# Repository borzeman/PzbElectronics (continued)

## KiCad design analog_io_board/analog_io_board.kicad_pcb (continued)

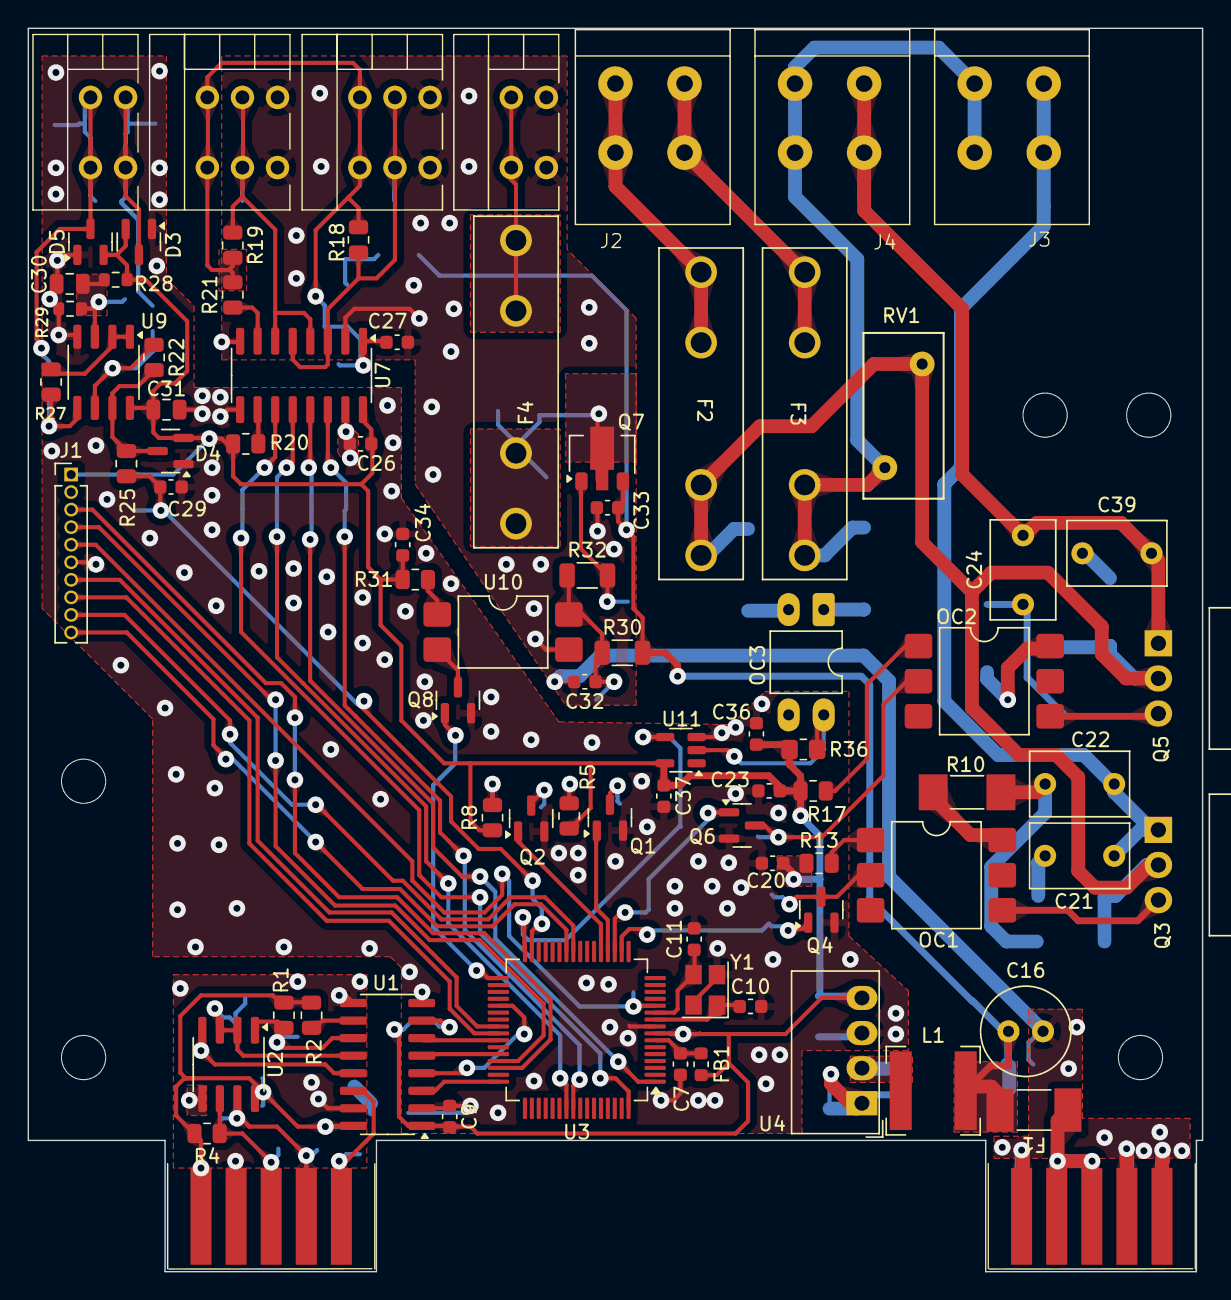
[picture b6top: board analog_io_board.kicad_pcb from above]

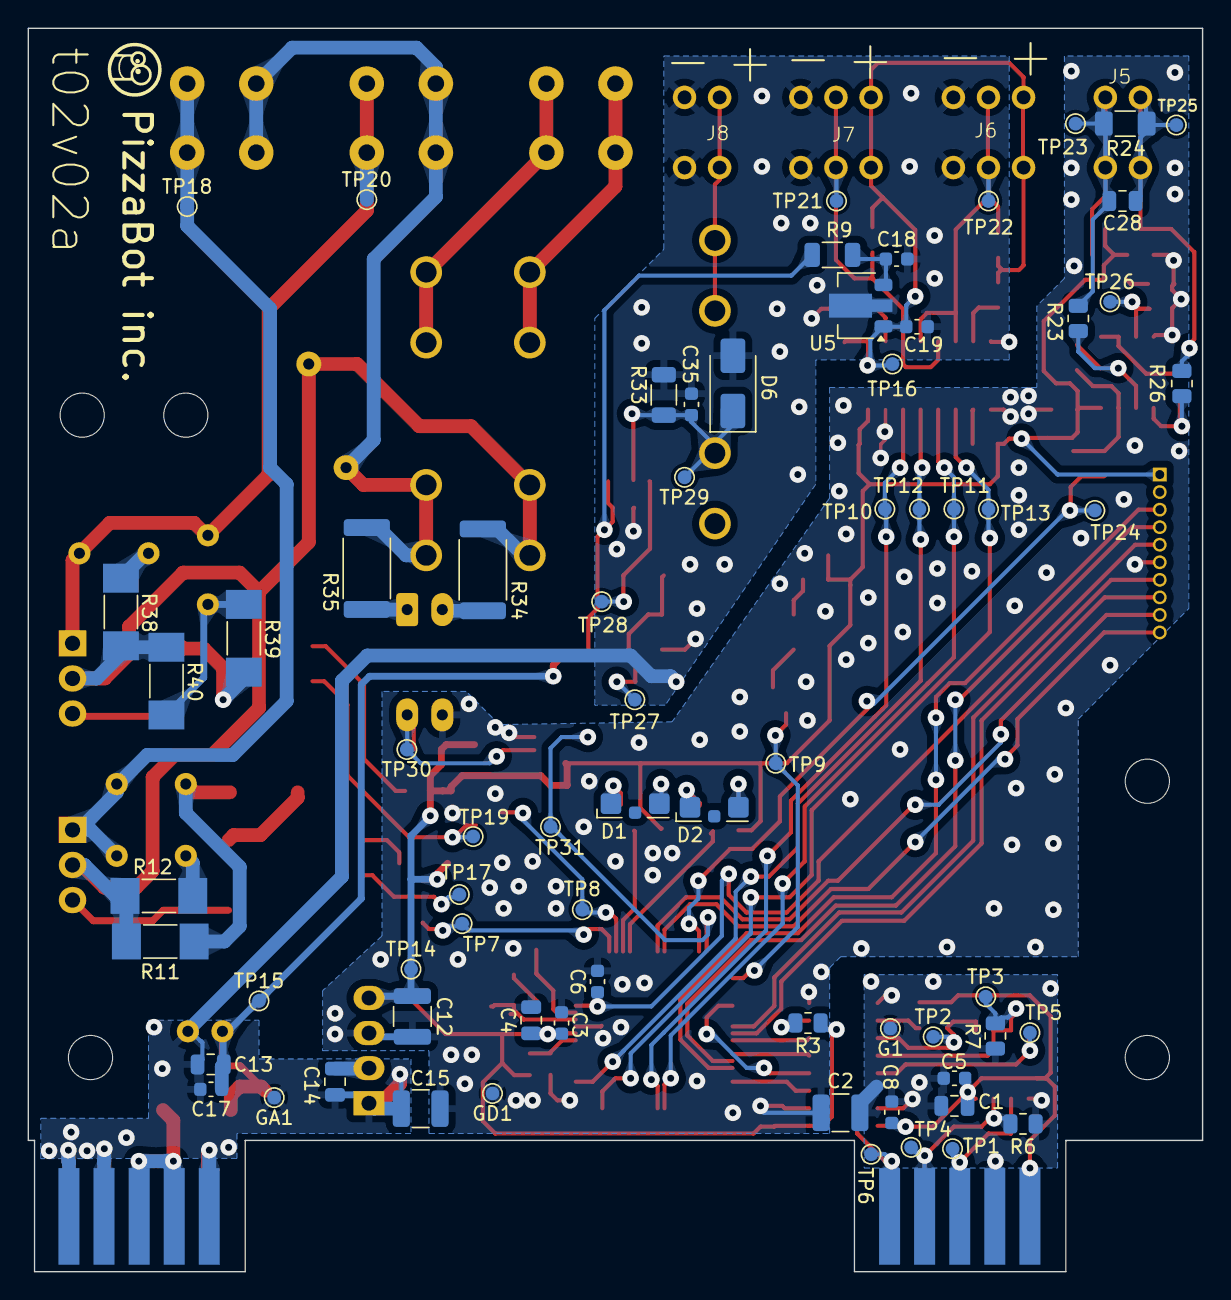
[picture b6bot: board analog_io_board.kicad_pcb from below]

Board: 2 copper layers, 85.0 x 90.0 mm, 156 parts (69 on the bottom side), 85 nets.

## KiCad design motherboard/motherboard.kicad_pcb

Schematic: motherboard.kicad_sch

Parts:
D1, D2, D3, D4, D5, D6, D7, D8, D9, D10: SMBJ5.0A (SMB); D_SMB
H1, H2, H3, H4, H5, H6, H7, H8, H9, H10, H11, H12, H13, H14: MountingHole_M3_3.2mm_Pad; MountingHole_3.2mm_M3
J1, J2, J4, J5, J6, J7, J8, J9, J10, J11, J12, J13, J14, J15, J16, J17, J18, J19, J20, J21, J22, J23, J24, J25: SL-10 (L-KLS1-603C-10-S)
J3: SL-14 (L-KLS1-603C-14-S)
J28: PinHeader_1x02_P2.54mm (Contr +24V); PinHeader_1x02_P2.54mm_Vertical
J29: PinHeader_1x04_P2.54mm (RS485); PinHeader_1x04_P2.54mm_Vertical
J30: PinHeader_2x07_P2.54mm (RTS); PinHeader_2x07_P2.54mm_Vertical
L2: B82790S0253N201; L_CommonMode_Delevan_4222
R1: 1206-120 Ом±5%-0,25 Вт; R_1206_3216Metric
RV1, RV2, RV3, RV4, RV5: JMV0805S5R6T661; R_0805_2012Metric
TP1, TP2, TP3, TP17: TestPoint; TestPoint_Pad_D1.0mm
TP4, TP5, TP6, TP7, TP8, TP9, TP10, TP11, TP12, TP13, TP14, TP15, TP16: TestPoint; TestPoint_D1

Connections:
+24V: J2.2, J2.3, J2.8, J2.9, J5.2, J5.3, J5.8, J5.9, J7.2, J7.3, J7.8, J7.9, J9.2, J9.3, J9.8, J9.9, J11.2, J11.3, J11.8, J11.9, J13.2, J13.3, J13.8, J13.9, J15.2, J15.3, J15.8, J15.9, J17.2, J17.3, J17.8, J17.9, J19.2, J19.3, J19.8, J19.9, J21.2, J21.3, J21.8, J21.9, J23.2, J23.3, J23.8, J23.9, J25.2, J25.3, J25.8, J25.9, J28.2, TP16.1; also elsewhere on the board
/+3.3VRS485: J1.1, J1.10, J4.1, J4.10, J6.1, J6.10, J8.1, J8.10, J10.1, J10.10, J12.1, J12.10, J14.1, J14.10, J16.1, J16.10, J18.1, J18.10, J20.1, J20.10, J22.1, J22.10, J24.1, J24.10, J29.1, TP15.1; also elsewhere on the board
/A: D1.1 (K), D4.1 (K), D6.1 (K), D8.1 (K), D10.1 (K), J4.3, J4.8, J6.3, J6.8, J8.3, J8.8, J10.3, J10.8, J12.3, J12.8, J14.3, J14.8, J16.3, J16.8, J18.3, J18.8, J20.3, J20.8, J22.3, J22.8, J24.3, J24.8, J29.3, L2.3, R1.1, RV1.1, RV2.1, RV3.1, RV4.1, RV5.1, TP1.1
/B: D2.1 (K), D3.1 (K), D5.1 (K), D7.1 (K), D9.1 (K), J4.4, J4.7, J6.4, J6.7, J8.4, J8.7, J10.4, J10.7, J12.4, J12.7, J14.4, J14.7, J16.4, J16.7, J18.4, J18.7, J20.4, J20.7, J22.4, J22.7, J24.4, J24.7, J29.4, L2.4, R1.2, RV1.2, RV2.2, RV3.2, RV4.2, RV5.2, TP2.1
/RTS1: J3.1, J4.5, J4.6, J30.1, TP3.1
/RTS2: J3.14, J6.5, J6.6, J30.2, TP9.1
/RTS3: J3.2, J8.5, J8.6, J30.3, TP4.1
/RTS4: J3.13, J10.5, J10.6, J30.4, TP10.1
/RTS5: J3.3, J12.5, J12.6, J30.5, TP5.1
/RTS6: J3.12, J14.5, J14.6, J30.6, TP11.1
/RTS7: J3.4, J16.5, J16.6, J30.7, TP6.1
/RTS8: J3.11, J18.5, J18.6, J30.8, TP12.1
/RTS9: J3.5, J20.5, J20.6, J30.9, TP7.1
/RTS10: J3.10, J22.5, J22.6, J30.10, TP13.1
/RTS11: J3.6, J24.5, J24.6, J30.11, TP8.1
/RTS12: J3.9, J30.12
GND1: D1.2 (A), D2.2 (A), D3.2 (A), D4.2 (A), D5.2 (A), D6.2 (A), D7.2 (A), D8.2 (A), D9.2 (A), D10.2 (A), J1.2, J1.5, J1.6, J1.9, J3.7, J3.8, J4.2, J4.9, J6.2, J6.9, J8.2, J8.9, J10.2, J10.9, J12.2, J12.9, J14.2, J14.9, J16.2, J16.9, J18.2, J18.9, J20.2, J20.9, J22.2, J22.9, J24.2, J24.9, J29.2, J30.13, J30.14, TP17.1; also elsewhere on the board
GNDA: J2.1, J2.4, J2.5, J2.6, J2.7, J2.10, J5.1, J5.4, J5.5, J5.6, J5.7, J5.10, J7.1, J7.4, J7.5, J7.6, J7.7, J7.10, J9.1, J9.4, J9.5, J9.6, J9.7, J9.10, J11.1, J11.4, J11.5, J11.6, J11.7, J11.10, J13.1, J13.4, J13.5, J13.6, J13.7, J13.10, J15.1, J15.4, J15.5, J15.6, J15.7, J15.10, J17.1, J17.4, J17.5, J17.6, J17.7, J17.10, J19.1, J19.4, J19.5, J19.6, J19.7, J19.10, J21.1, J21.4, J21.5, J21.6, J21.7, J21.10, J23.1, J23.4, J23.5, J23.6, J23.7, J23.10, J25.1, J25.4, J25.5, J25.6, J25.7, J25.10, J28.1, TP14.1; also elsewhere on the board
unnamed: J1.3, J1.8, L2.2
unnamed: J1.4, J1.7, L2.1

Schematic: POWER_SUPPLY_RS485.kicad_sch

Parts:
C3: 10uF 50V 1210 GRM32ER71H106K; C_1210_3225Metric
C4, C5: 4,7uF 50V 0805; C_0805_2012Metric
C6: 270 pf X7R 1206 2000v 202R18W271KW4E; C_1210_3225Metric
D14: LED 0805 (FYLS-0805UBC); LED_0805_2012Metric_Pad1.15x1.40mm_HandSolder
L1: 6,8uH 3,5A ETQP3M6R8KVP; L_Bourns-SRN6028
R8: 0805-200 Ом±5%-0,125 Вт; R_0805_2012Metric
U2: AM1SS-2403SJZ; Converter_DCDC_Murata_CRE1xxxxxx3C_THT

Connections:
+24V: C4.1, L1.1; also elsewhere on the board
/+3.3VRS485: C3.1, D14.2 (A), U2.4 (OUT+); also elsewhere on the board
GND1: C3.2, C6.2, R8.2, U2.3 (OUT-); also elsewhere on the board
GNDA: C4.2, C5.2, C6.1, U2.1 (IN-); also elsewhere on the board
unnamed: D14.1 (K), R8.1
unnamed: C5.1, L1.2, U2.2 (IN+)

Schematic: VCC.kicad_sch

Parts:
C1, C2: 47uF 63V D10 H16; CP_Radial_D10.0mm_P5.00mm
C7: 0,01uF 50V 0805; C_0805_2012Metric
D11: SM6T27CA (SMB); D_SMB
D12: LED 0805 (FYLS-0805UBC); LED_0805_2012Metric_Pad1.15x1.40mm_HandSolder
D13: BZX84C10 (SOT-23); SOT-23
F1, F2: Fuse 5A ZH266 (2 клипсы); Fuseholder_Littelfuse_100_series_5x20mm
FL1: ACM70V-701-2PL-TL00; ACM12V
J26, J27: DG142V-5.08-02P-14
Q1, Q3: SUM110P06-08L-E3 (TO-263-2); TO-263-2
Q6: PMBT3906; SOT-23-3
Q7: TS820-600B; TO-252-2
R2: 2512-2,4 кОм±5%-1 Вт; R_2512_6332Metric
R3, R7, R12: 0805-10 кОм±5%-0,125 Вт; R_0805_2012Metric
R4: 0805-1,5 кОм±5%-0,125 Вт; R_0805_2012Metric
R5, R6: 1206-1 кОм±5%-0,25 Вт; R_1206_3216Metric
R9: 0805-100 кОм±5%-0,125 Вт; R_0805_2012Metric
R10: 0805-11 кОм±5%-0,125 Вт; R_0805_2012Metric
R11: 1206-3,3 кОм±5%-0,25 Вт; R_1206_3216Metric
R13: 0805-7,5 кОм±5%-0,125 Вт; R_0805_2012Metric
R14: 0805-1 кОм±5%-0,125 Вт; R_0805_2012Metric
R15: 0805-56 кОм±5%-0,125 Вт; R_0805_2012Metric
TP18, TP19: TestPoint; TestPoint_Pad_D1.0mm
TP20: TestPoint; TestPoint_D1
U1, U3: TL431DBZ (sot-23); SOT-23

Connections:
+24V: C2.1, D12.2 (A), FL1.4; also elsewhere on the board
GNDA: C2.2, FL1.3, R2.2; also elsewhere on the board
unnamed: D11.1 (A1), F1.1, Q3.2 (D), Q7.2 (A), R9.1, R11.1, R13.1
unnamed: C1.2, C7.2, D11.2 (A2), F2.1, FL1.2, Q7.1 (K), R4.2, R7.2, R10.2, R14.2, R15.2, TP20.1, U1.3 (A), U3.3 (A)
unnamed: D12.1 (K), R2.1
unnamed: D13.1 (A), Q3.1 (G), R7.1
unnamed: D13.3 (K), Q1.3 (S), Q3.3 (S), R3.1, R5.1, TP19.1
unnamed: F1.2, J26.1, J26.2
unnamed: F2.2, J27.1, J27.2
unnamed: C1.1, FL1.1, Q1.2 (D), TP18.1
unnamed: Q1.1 (G), R5.2, R6.1
unnamed: Q6.1 (B), R12.2
unnamed: C7.1, Q6.3 (C), Q7.3 (G), R14.1
unnamed: Q6.2 (E), R13.2
unnamed: R6.2, U1.1 (K)
unnamed: R3.2, R4.1, U1.2 (REF)
unnamed: R11.2, R12.1, U3.1 (K)
unnamed: R9.2, R10.1, R15.1, U3.2 (REF)

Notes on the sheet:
защита от обратной полярности
10V
защита от низкого напряжения
напряжение в открытом состоянии 0,9V
защита от перенапряжения
2,5V срабатывания
1.2mA
0,125mA 15V

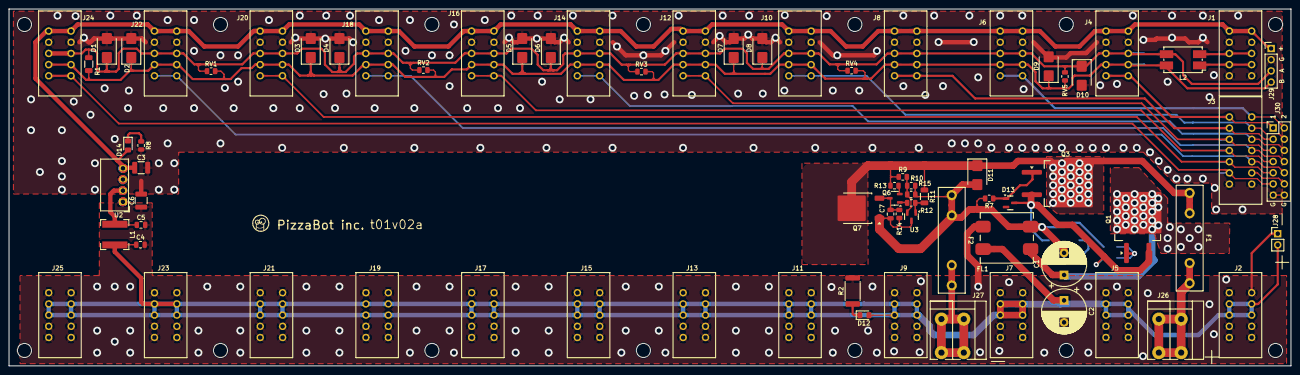
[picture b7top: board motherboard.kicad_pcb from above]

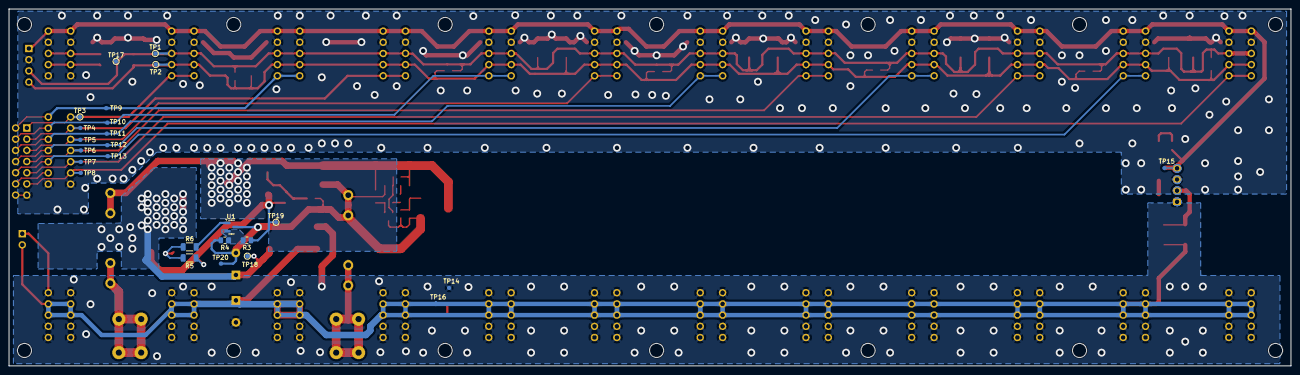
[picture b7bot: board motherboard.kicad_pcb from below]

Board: 2 copper layers, 291.0 x 81.0 mm, 117 parts (25 on the bottom side), 38 nets.

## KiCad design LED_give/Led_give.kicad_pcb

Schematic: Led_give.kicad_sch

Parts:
C1: 100uF 50V 10x10,5(JCK1H101M100105); CP_Elec_10x10.5
C2, C3, C4: 0,1uF 100V 0805; C_0805_2012Metric
D1, D2, D3: BZV55B10; D_MiniMELF
F1: Fuse 5A ZH266 (2 клипсы); Fuseholder_100_series_5x20mm_D1,5
H1, H2: MountingHole; MountingHole_3.2mm_M3_Pad
J1: DG141R-2.54-02P-14-00; DG141R-04
J2: DG142R-5.08-04P-14
J3: DG142R-5.08-02P-14
Q1, Q2, Q3: 50N06; TO-252-2
R1, R3, R5: 203; R_0805_2012Metric
R2, R4, R6: 752; R_0805_2012Metric

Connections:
+24V: C1.1, F1.1, J2.1
/Bin: C4.1, J1.4, R5.1
/Bout: J2.4, Q3.2 (D)
/Gin: C3.1, J1.3, R3.1
/Gout: J2.3, Q2.2 (D)
/Rin: C2.1, J1.2, R1.1
/Rout: J2.2, Q1.2 (D)
GND: C1.2, C2.2, C3.2, C4.2, D1.2 (A), D2.2 (A), D3.2 (A), J1.1, J3.2, Q1.3 (S), Q2.3 (S), Q3.3 (S), R2.1, R4.1, R6.1
unnamed: D1.1 (K), Q1.1 (G), R1.2, R2.2
unnamed: D2.1 (K), Q2.1 (G), R3.2, R4.2
unnamed: D3.1 (K), Q3.1 (G), R5.2, R6.2
unnamed: F1.2, J3.1

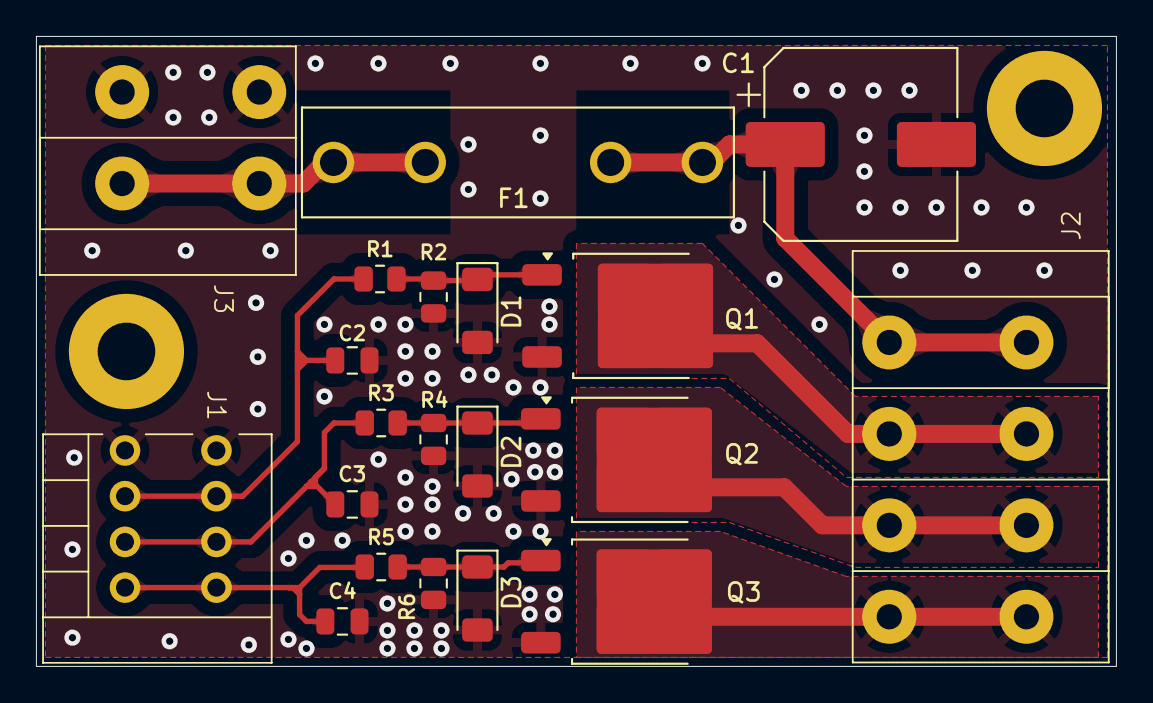
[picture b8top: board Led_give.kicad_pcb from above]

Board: 2 copper layers, 60.0 x 35.0 mm, 22 parts (0 on the bottom side), 12 nets.

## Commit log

2024-04-30 Added technical specifications
2024-04-30 Загрузка файлов первоначальная
2024-04-30 add txt
2024-04-30 add first file
2024-05-01 MB added protect,LED
2024-05-01 deleted unnecessary file
2024-05-04 Modify Digit_IN, Motherbord, Step motors
2024-05-07 Modify Digit_IN, Motherbord, Step motors, photo
2024-05-20 Modify Motherbord Schems and PCB
2024-05-20 Modify Motherbord Schems and PCB1
2024-05-22 Modify MainController Schems and PCB1
2024-05-22 Modify Pump Schems and PCB1
2024-05-22 Modify Triac Schems and PCB1
2024-05-22 Modify StepMotor Schems and PCB1
2024-05-22 Modify DiscretIN Schems and PCB1
2024-05-27 Modify Mian controller, stepmotor, motor 25.05.24
2024-06-03 Add DE USART 03.06.24
2024-06-03 Change ISOLATOR 03.06.24
2024-06-05 pcb and schems step 05.06.24
2024-06-07 pcb and schems main controller 07.06.24
2024-06-10 renew motherbord (tvs) and new dc_motors 10.06.24
2024-06-10 stepmotor add r41 10.06.24
2024-06-11 Discret IN OUT schems
2024-06-13 LED PhotoTrans schems and PCB
2024-06-17 Triak schems and PCB
2024-06-18 Change TVS diods near optopair schems and PCB
2024-06-18 add analog board reqs
2024-06-18 Main controller +3.3V RS485 schems and PCB
2024-06-25 DIgit_IN renew schems
2024-06-26 Main controller renew schems and PCB
2024-06-26 renew schems
2024-06-27 remove excess files
2024-06-27 fotodiod sborochniy1
2024-06-27 DC motor schems
2024-06-28 Discret IN_OUT schems and PCB
2024-07-02 Renew footprint connectors PCB
2024-07-03 Renew pin Prog connectors and schem Analog IO
2024-07-04 digit IO terned LED
2024-07-05 renew all schems and pcb for production
2024-07-10 add relay control to analog board requirements
2024-07-10 PCB AND SCHEMS DC MOTOR
2024-07-11 analog io control relay added
2024-07-11 analog io control relay added1
2024-07-17 anlog IO pcb and shcems
2024-07-18 add reqs to analog board to make it suitable for fridge control
2024-07-19 anlog IO shcems 2.0
2024-07-22 anlog IO shcems 2.1
2024-07-23 QR code schems
2024-07-23 RENEW Analog IO schems
2024-07-25 QR board reqs
2024-07-26 qr code 1.1
2024-07-27 analog board add mech relay diode requirement
2024-07-27 Remove relay signal current limiting requirement
2024-07-28 RENEW ALL BOARDS
2024-07-31 CHANGE CONNECTORS ON DG245
2024-08-01 IO ANALOG PCB
2024-08-08 qr code schems and pcb
2024-08-12 update qr reqs
2024-08-23 qr and analog refresh
2024-09-26 fix "pia" typo
2024-10-03 rename files to snake case matching with their dir
2024-11-18 DCmotors V1.5
2024-11-20 add manipulator attachment scheme
2024-11-20 fix dc board issues before manufacturing
2024-11-21 DC, contr, mb, step v2
2024-11-21 digit_in v2
2024-11-25 DC, contr, mb, digit in v2.1
2024-11-26 step v2.1
2024-11-27 Triak v2.1
2024-11-29 manipulator 1.0
2024-12-02 controller убраны ловушки
2024-12-02 digit_in убраны ловушки
2024-12-02 step убраны ловушки
2024-12-02 mother убраны ловушки
2024-12-02 created integration tests for all boards
2024-12-04 Step установлена бусинка
2024-12-04 changing the structure of integration tests
2024-12-05 led_and_photo замена цепь формирования выходного сигнала
2024-12-06 Step кондеры pai
2024-12-06 Step кислотные ловушки убраны
2024-12-06 rm skvd
2024-12-06 motherboard установлены тестовые площадки
2024-12-06 controller метализированные отверстия
2024-12-06 controller тестовые площадки
2024-12-06 Test scripts written, firmware description added
2024-12-06 controller кислотные ловушки
2024-12-06 controller кислотные ловушки1
2024-12-06 dc утолщение силовой части
2024-12-06 dc Pai capasitor
2024-12-06 dc шелкография
2024-12-07 digit in ловушки
2024-12-07 manipulator ловушки
2024-12-07 manipulator крепежные отверстия
2024-12-07 ledphoto исправлена микросхема
2024-12-07 step исправлены ловушки
2024-12-07 controller кондеры pai на одной стороне
2024-12-07 controller кондеры pai на одной стороне 2
2024-12-07 triak уменьшение нагрева
2024-12-07 digit in test point
2024-12-08 ledphoto коррекция схемы
2024-12-09 minor changes
2024-12-10 Triak поправлен нагрев дорожек
2024-12-10 культя добавлен логотип
2024-12-10 Pre-final version of test cases for integration tests + description of functions
2024-12-11 ledphoto обновление питания светодиодов
2024-12-11 update led's requirements
2024-12-11 update controller's requirements
2024-12-11 add common boards' requirements
2024-12-11 update mother's requirements
2024-12-11 add raw list of boards' requirements
2024-12-11 udpate dc requirements
2024-12-11 update qr's requirements
2024-12-11 update step's requirements
2024-12-11 update di's board requirements
2024-12-11 update triac's requirements
2024-12-12 Scenario #12 is updated, the block with the description of connections is completed to the end.
2024-12-15 updated firmware description
2024-12-16 Scenario Check 11
2024-12-16 integration test conds
2024-12-17 Added program source code to verify coverage with tests. Added coverage data for actual tests
2024-12-17 ledphoto обновлена схема и pcb
2024-12-17 ledphoto скругление на заливках
2024-12-19 The structure of test scenarios has been changed. The file with test conditions has been supplemented. Test coverage map updated.
2024-12-20 ledphoto замена компаратора на операционник, добавлен снаббер
2024-12-20 triak обновлен снаббер
2024-12-20 triak убраны тестовые площадки с 220в
2024-12-20 all замменил резисторы failsafe в плате контроллера и обрал из перечня во всех остальных
2024-12-20 triak снаббер
2024-12-21 triak снаббер pcb
2024-12-24 The first script is completely rewritten. Fixed firmware descriptions
2024-12-26 step,mother,digitin,dc,controller электронные сборочные
2024-12-27 Rewritten 2nd script, updated firmware descriptions
2024-12-30 the third script has been rewritten
2024-12-30 manipulator углы и терминатор
2025-01-08 led and photo топология
2025-01-10 Scripts 3 and 4 have been rewritten. Updated coverage map for 1-4 scenarios. Added firmware description for scenario 4. Added new test conditions. Renumbered tests 5-6, 6-5. Started work on scenario 5
2025-01-14 Finalized scenario 5, updated firmware description file
2025-01-16 Edits made after the review
2025-01-17 The coverage map is now correct
2025-01-20 The text description of firmware for the 5th scenario has been translated into a feature set, and several new features have been added. minor text corrections
2025-01-22 fix markdown headers' structure
2025-01-27 minor fixes
2025-03-14 unify operator's signals
2025-03-14 remove excess test
2025-03-14 rewrite RTS power interrupt logic
2025-03-25 temoporary remove 5th and 6th scenarios
    with their conditions, functions and firmware
2025-03-25 remove excess di inputs checking
    only one firmware actually needs checking, moved it to a comment
2025-03-25 remove dang func link
2025-03-25 add missed power turning
2025-03-25 clarify parad testing
2025-03-26 update rts and parad tests
    rts now is fully checked by firmware
2025-03-26 separate stepper noise, real load and max 24v load
2025-03-26 separate dc noise, real load and max 24v load
2025-03-26 separate triac noise, real load and max 24v load
2025-03-26 remove sensors tests
    will add them in new tests
2025-03-26 separate analog noise, real load and max 24v load
2025-03-26 check qr fully with firmware
2025-03-26 clarify temp and cur measurement
2025-03-26 fix links and unused functions
2025-03-27 return limit switch testing
2025-03-27 return current testing
2025-03-27 return photosensors testing
2025-03-28 refactor: remove dead code
2025-03-28 refactor: fix numbering
2025-03-28 remove operator's start signal
    now tests start after a power up
2025-03-28 refactor: inline single func description
2025-03-28 remove excess slave boards signals from test 1
    master's signals are enough
2025-03-28 remove slave boards signals for lim and photo tests
    now only master signals about test's state
2025-03-28 remove excess signals from slave boards
2025-03-28 add missed commands and signals
2025-03-28 remove operator's start signals and move signals to master
2025-03-28 remove parad function from sensors tests
    "previous firmwares" (*_013) use usart for rs testing, which collides
    with usart signals for sensors tests
2025-03-28 add temperature test
2025-03-28 separate QR checking and noise/load
2025-03-28 add master checking for QR errors
    firmwares was combined cause they are actually identical
2025-03-28 remove unrelated checks and signals from real scenarios tests
    no need for start command - starting after a power up
    no need for signals either - only temp and behaviour should be validated
2025-03-28 remove slaves signals from max load tests
2025-03-28 remove signals and start command from (under-)overvoltage tests
2025-03-28 clarify commands and signals; remove unreferenced function
2025-03-29 refactor: remove unused functions
2025-03-29 extract duplicated firmware
2025-04-04 QRcode udate size and schems
2025-04-04 added units
2025-04-05 change cut schems
2025-04-09 add LED_give
2025-04-09 add LED_give PCB
2025-04-10 refresh ledfotodiod
2025-04-30 remove temp sensors tests
2025-04-30 remove 2nd analog board
2025-05-05 remove current sensor test
2025-05-05 different firmwares for parad tests
2025-05-05 different firmwares for parad tests (scenario 4)
2025-05-07 remove master_040 reference cause it's not used
2025-05-12 remove unused debug usart connection
2025-05-21 mother board refresh
2025-06-02 analog board refresh
2025-06-10 analog board refresh pcb
2025-09-25 remove accidental binary
2025-10-31 update schemas
2025-10-31 add missed sheets
